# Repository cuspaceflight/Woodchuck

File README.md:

# Woodchuck
2015/2016 HAB project

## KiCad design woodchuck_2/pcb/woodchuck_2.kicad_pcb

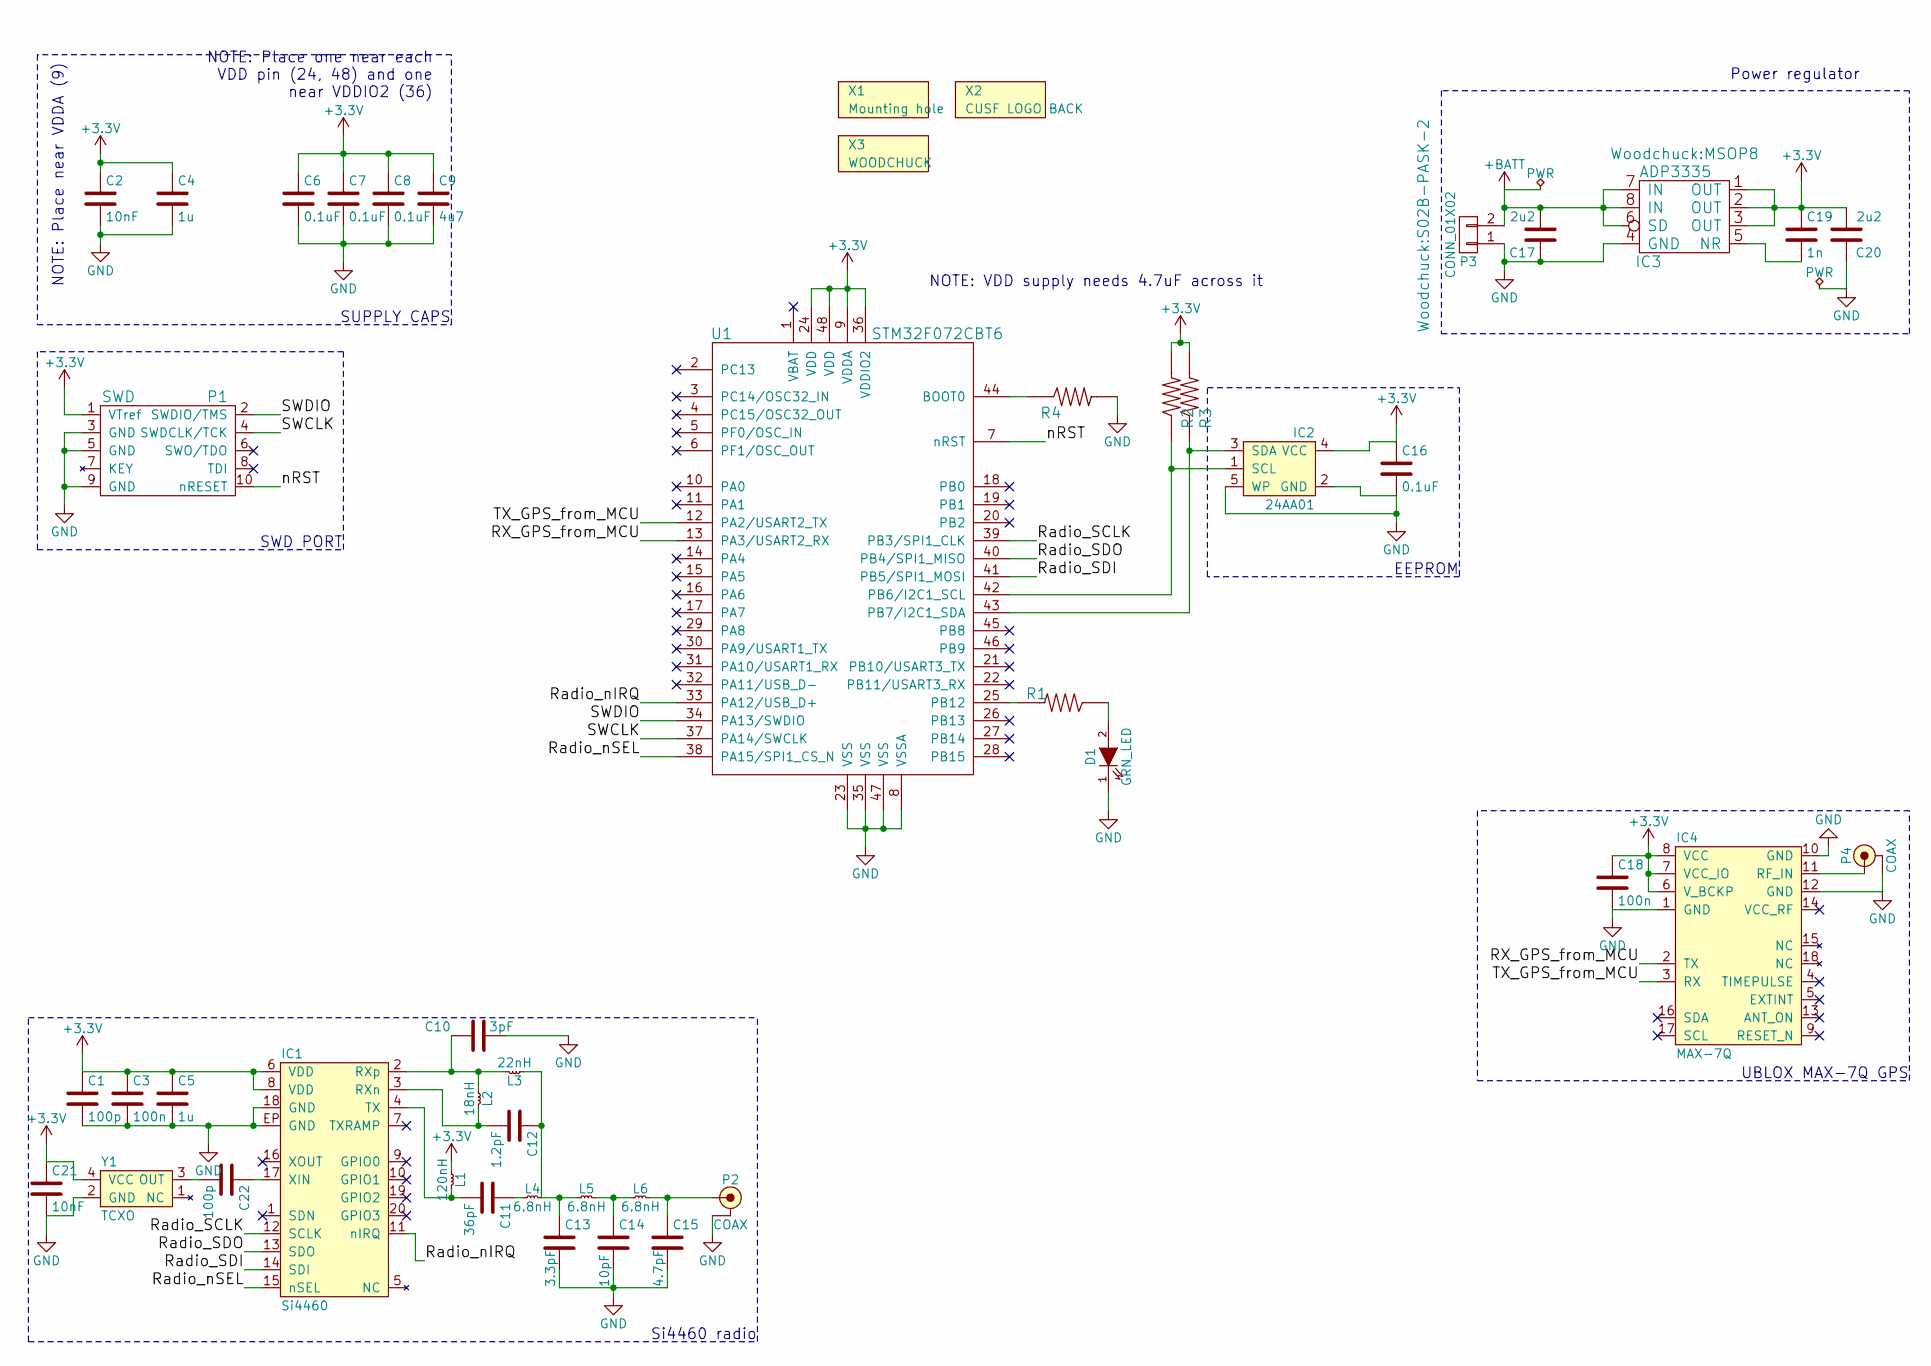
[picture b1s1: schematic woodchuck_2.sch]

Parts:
C1, C22: 100p; 0402; Digikey Value
C2, C21: 10nF; 0402; Digikey Value
C3, C18: 100n; 0402; Digikey Value
C4, C5: 1u; 0402; Digikey Value
C6, C7, C8, C16: 0.1uF; 0402; Digikey Value
C9: 4u7; 0402; Digikey Value
C10: 3pF; 0402; Digikey Value
C11: 36pF; 0402; Digikey Value
C12: 1.2pF; 0402; Digikey Value
C13: 3.3pF; 0402; Digikey Value
C14: 10pF; 0402; Digikey Value
C15: 4.7pF; 0402; Digikey Value
C17, C20: 2u2; 0603; Digikey Value
C19: 1n; 0402; Digikey Value
D1: GRN_LED; 0603-LED; Digikey Value
IC1: Si4460; QFN-20-EP-SI; Farnell 2462635
IC2: 24AA01; SOT-23-5; Farnell 1331269
IC3: ADP3335; MSOP8; Digikey Value
IC4: MAX-7Q; Digikey Value
L1: 120nH; 0603-L; Digikey Value
L2: 18nH; 0603-L; Digikey Value
L3: 22nH; 0603-L; Digikey Value
L4, L5, L6: 6.8nH; 0603-L; Digikey Value
P1: SWD; FTSH-105-01-F-D-K; Digikey Value
P2, P4: COAX; SMA-142-0701-801; Digikey Value
P3: CONN_01X02; S02B-PASK-2; Digikey Value
R1: 510; 0402; Digikey Value
R2, R3, R4: 10K; 0402; Digikey Value
U1: STM32F072CBT6; LQFP48; Digikey Value
X1: Mounting hole; M3_MOUNT
X2: CUSF LOGO BACK; cusf_logo_small; Digikey Value
X3: WOODCHUCK; Woodchuck_2; Digikey Value
Y1: TCXO; TG-5006CJ; Digikey Value

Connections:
+3V3: C1.1, C2.1, C3.1, C4.1, C5.1, C6.1, C7.1, C8.1, C9.1, C16.1, C18.1, C19.1, C20.2, C21.1, IC1.6 (VDD), IC1.8 (VDD), IC2.4 (VCC), IC3.1 (OUT), IC3.2 (OUT), IC3.3 (OUT), IC4.6 (V_BCKP), IC4.7 (VCC_IO), IC4.8 (VCC), L1.1, P1.1 (VTref), R2.1, R3.1, U1.9 (VDDA), U1.24 (VDD), U1.36 (VDDIO2), U1.48 (VDD), Y1.4 (VCC)
+BATT: C17.2, IC3.6 (SD), IC3.7 (IN), IC3.8 (IN), P3.2
/RX_GPS_from_MCU: IC4.2 (TX), U1.13 (PA3/USART2_RX)
/Radio_SCLK: IC1.12 (SCLK), U1.39 (PB3/SPI1_CLK)
/Radio_SDI: IC1.14 (SDI), U1.41 (PB5/SPI1_MOSI)
/Radio_SDO: IC1.13 (SDO), U1.40 (PB4/SPI1_MISO)
/Radio_nIRQ: IC1.11 (nIRQ), U1.33 (PA12/USB_D+)
/Radio_nSEL: IC1.15 (nSEL), U1.38 (PA15/SPI1_CS_N)
/SWCLK: P1.4 (SWDCLK/TCK), U1.37 (PA14/SWCLK)
/SWDIO: P1.2 (SWDIO/TMS), U1.34 (PA13/SWDIO)
/TX_GPS_from_MCU: IC4.3 (RX), U1.12 (PA2/USART2_TX)
/nRST: P1.10 (nRESET), U1.7 (nRST)
GND: C1.2, C2.2, C3.2, C4.2, C5.2, C6.2, C7.2, C8.2, C9.2, C10.2, C13.2, C14.2, C15.2, C16.2, C17.1, C18.2, C20.1, C21.2, D1.1 (K), IC1.18 (GND), IC1.EP (GND), IC2.2 (GND), IC2.5 (WP), IC3.4 (GND), IC4.1 (GND), IC4.10 (GND), IC4.12 (GND), P1.3 (GND), P1.5 (GND), P1.9 (GND), P2.2 (GND), P3.1, P4.2 (GND), R4.1, U1.8 (VSSA), U1.23 (VSS), U1.35 (VSS), U1.47 (VSS), Y1.2 (GND)
unnamed: C10.1, IC1.2 (RXp), L2.1, L3.2
unnamed: C11.1, L4.1
unnamed: C11.2, IC1.4 (TX), L1.2
unnamed: C12.1, C13.1, L3.1, L4.2, L5.1
unnamed: C12.2, IC1.3 (RXn), L2.2
unnamed: C14.1, L5.2, L6.1
unnamed: C15.1, L6.2, P2.1 (RF)
unnamed: C19.2, IC3.5 (NR)
unnamed: C22.1, IC1.17 (XIN)
unnamed: C22.2, Y1.3 (OUT)
unnamed: D1.2 (A), R1.2
unnamed: IC2.1 (SCL), R2.2, U1.42 (PB6/I2C1_SCL)
unnamed: IC2.3 (SDA), R3.2, U1.43 (PB7/I2C1_SDA)
unnamed: IC4.11 (RF_IN), P4.1 (RF)
unnamed: R1.1, U1.25 (PB12)
unnamed: R4.2, U1.44 (BOOT0)

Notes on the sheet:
Power regulator
NOTE: Place one near each VDD pin (24, 48) and one near VDDIO2 (36)
NOTE: Place near VDDA (9)
NOTE: VDD supply needs 4.7uF across it
SWD PORT
SUPPLY CAPS
EEPROM
UBLOX MAX-7Q GPS
Si4460 radio

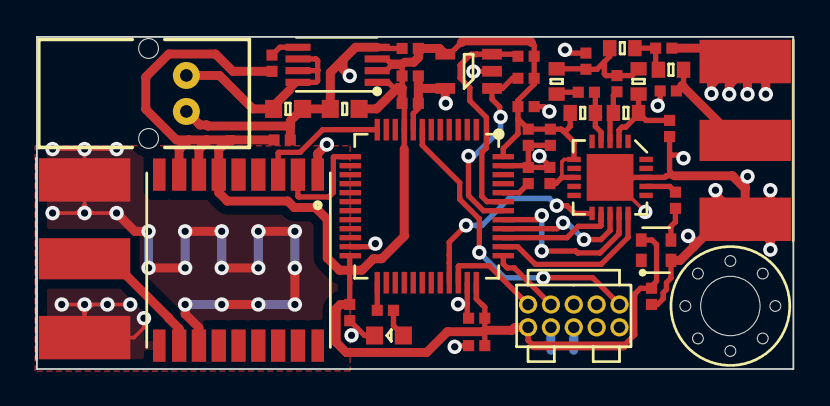
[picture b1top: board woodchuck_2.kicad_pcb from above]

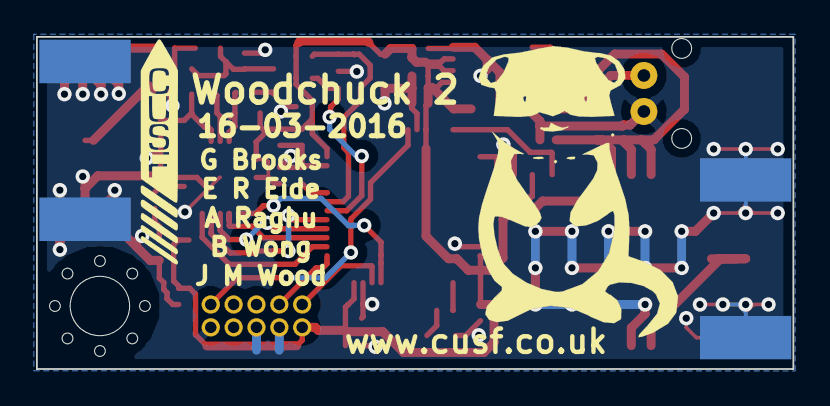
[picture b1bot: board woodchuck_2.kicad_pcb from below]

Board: 2 copper layers, 42.0 x 18.5 mm, 46 parts (2 on the bottom side), 29 nets.

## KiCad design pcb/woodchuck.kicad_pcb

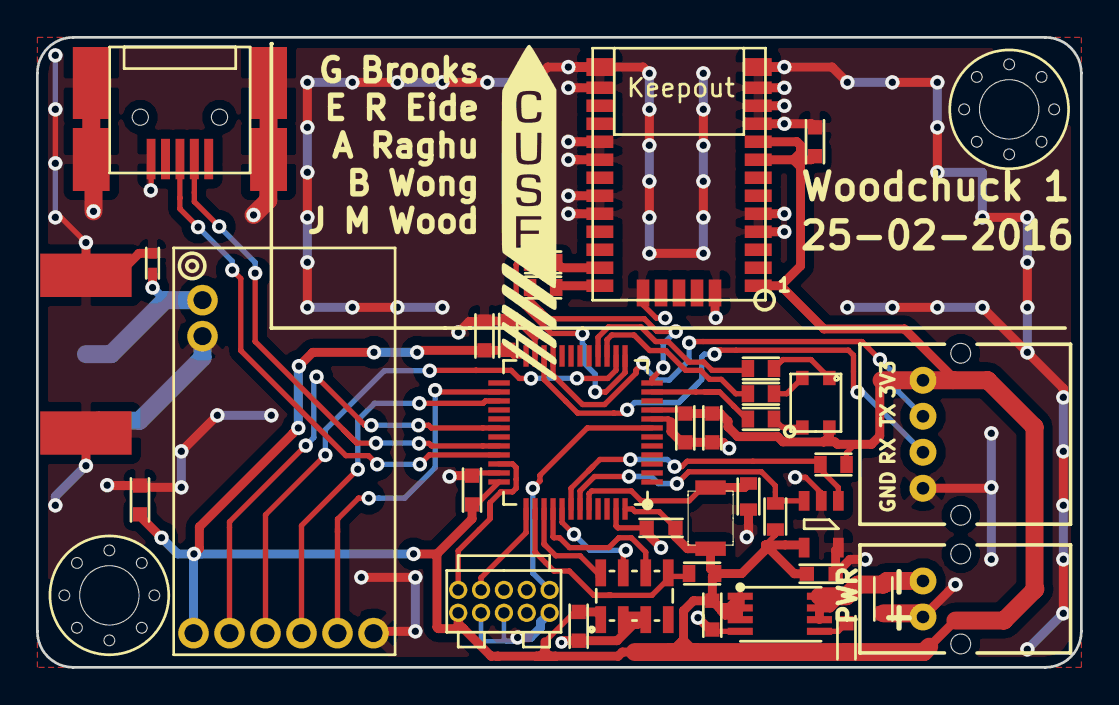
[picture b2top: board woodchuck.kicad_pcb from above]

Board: 2 copper layers, 58.0 x 35.0 mm, 40 parts (1 on the bottom side), 34 nets.

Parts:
A301: SMA; SMA-142-0701-801
C1, C402, C403, C404: 0.1uF; C0603
C101, C103: 2u2; C0603
C102: 1n; C0603
C201, C301, C601: 100n; C0603
C401: 10nF; C0603
C405: 1u; C0603
C406: 4u7; C0603
D301: CGA0402MLC-12G; R0402
D401: LED_RABG; CREE_RGB_LED
IC1: 24AA01; SOT-23-5
IC101: ADP3335; MSOP8
IC201: u-blox_CAM-M8Q; UBLOX_CAM_M8Q
IC601: MS5611-01BA03; MS5611-01BA
J401: JSTA-4; S04B-PASK-2
P101: CONN_01X02; S02B-PASK-2
P401: SWD; FTSH-105-01-F-D-K
P402: USB_OTG; MOLEX_67503_1020_MINI_USB
R1, R2, R404: 10K; 0603
R201, R202: 220; 0603
R401, R402, R403: 510; 0603
R601: 10k; 0603
SW401: SPST; B3U-1000P_switch
U301: Radiometrix_MTX2; MTX2
U401: STM32F072CBT6; LQFP48
X401, X402: Mounting hole; M3_MOUNT
X403: CUSF LOGO; cusf_logo
X404: CUSF LOGO BACK; cusf_logo_full

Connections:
+3V3: C1.1, C102.1, C103.1, C201.2, C301.1, C401.1, C402.1, C403.1, C404.1, C405.1, C406.1, C601.1, D401.2, IC1.4, IC101.1, IC101.2, IC101.3, IC201.1, IC201.8, IC201.9, IC601.1, J401.1, P401.1, R1.1, R2.1, R601.1, SW401.2, U301.3, U401.9, U401.24, U401.36, U401.48
+BATT: C101.2, IC101.6, IC101.7, IC101.8, P101.1
/GPS/GPS_FROM_MCU: R202.1, U401.12
/GPS/GPS_TO_MCU: R201.1, U401.13
/Radio/MTX2_EN/PGM: U301.4, U401.30
/Radio/MTX2_P0: U301.7, U401.26
/Radio/MTX2_P1: U301.6, U401.27
/Radio/MTX2_TXD: U301.5, U401.14
/barometer/BARO_CS: IC601.5, R601.2, U401.38
/barometer/BARO_MISO: IC601.6, U401.40
/barometer/BARO_MOSI: IC601.7, U401.41
/microcontroller/BARO_CLK: IC601.8, U401.39
/microcontroller/BOOT0: R404.1, SW401.1, U401.44
/microcontroller/EXT_RX: J401.3, U401.22
/microcontroller/EXT_TX: J401.2, U401.21
/microcontroller/SWCLK: P401.4, U401.37
/microcontroller/SWDIO: P401.2, U401.34
/microcontroller/USB_D+: P402.3, U401.33
/microcontroller/USB_D-: P402.2, U401.32
/microcontroller/nRST: P401.10, U401.7
GND: A301.2, A301.3, A301.4, A301.5, C1.2, C101.1, C103.2, C201.1, C301.2, C401.2, C402.2, C403.2, C404.2, C405.2, C406.2, C601.2, D301.2, IC1.2, IC1.5, IC101.4, IC201.4, IC201.5, IC201.10, IC201.11, IC201.12, IC201.13, IC201.14, IC201.15, IC201.18, IC201.19, IC201.21, IC201.22, IC201.27, IC201.31, IC601.2, IC601.3, J401.4, P101.2, P401.3, P401.5, P401.9, P402.5, P402.6, R404.2, U301.2, U301.8, U401.8, U401.23, U401.35, U401.47
unnamed: A301.1, D301.1, U301.1
unnamed: C102.2, IC101.5
unnamed: D401.1, R401.1
unnamed: D401.3, R403.1
unnamed: D401.4, R402.1
unnamed: IC1.1, R1.2, U401.42
unnamed: IC1.3, R2.2, U401.43
unnamed: IC201.16, IC201.17
unnamed: IC201.25, R201.2
unnamed: IC201.26, R202.2
unnamed: R401.2, U401.11
unnamed: R402.2, U401.15
unnamed: R403.2, U401.16

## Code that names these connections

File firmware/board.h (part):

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 *
 * PA0  - PIN0                         (unused).
 * PA1  - LED_RED                      (output, opendrain).
 * PA2  - GPS_TX                       (af1).
 * PA3  - GPS_RX                       (af1).
 * PA4  - RADIO_TX_DATA                (analog).
 * PA5  - LED_GREEN                    (output, opendrain).
 * PA6  - LED_BLUE                     (output, opendrain).
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 * PA9  - RADIO_EN_PIN                 (af1).
 * PA10 - USART_1_RX                   (af1).
 * PA11 - PIN11                        (unused).
 * PA12 - PIN12                        (unused).
 * PA13 - SWDIO                        (af0).
 * PA14 - SWCLK                        (af0).
 * PA15 - BARO_NCS                     (af0).
*/
#define VAL_GPIOA_MODER                (PIN_MODE_INPUT(GPIOA_PIN0) | \
                                        PIN_MODE_OUTPUT(GPIOA_LED_RED) | \
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 * PB0  - PIN0                         (unused).
 * PB1  - PIN1                         (unused).
 * PB2  - PIN2                         (unused).
 * PB3  - BARO_CLK                     (af0).
 * PB4  - BARO_MISO                    (af0).
 * PB5  - BARO_MOSI                    (af0).
 * PB6  - PIN6                         (unused).
 * PB7  - PIN7                         (unused).
 * PB8  - PIN8                         (unused).
 * PB9  - PIN9                         (unused).
 * PB10 - PIN10                        (unused).
 * PB11 - PIN11                        (unused).
 * PB12 - PIN12                        (unused).
 * PB13 - RADIO_CHANNEL_LSB            (output).
 * PB14 - RADIO_CHANNEL_MSB            (output).
 * PB15 - PIN15                        (unused).
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
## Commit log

2015-11-05 Added folders for PCB design and Firmware
2015-11-05 Added a KiCAD project
2015-11-05 Updated the info for the PCB
2015-11-05 Update pcbinfo.txt
    Added GPS info
2015-11-20 Create u-blox CAM-M8Q component and add avionics14 libraries to pcb folder
2015-11-26 Ani- Added supersheetsgit status
2015-11-27 Add radiometrix mtx2 schematic component
2015-11-29 Add STM32F072CBT6 library and microcontroller sheet
2015-11-29 Add SWD port to microcontroller sheet
2015-11-29 Add JSTA-4 connector
2015-11-29 Add USB connector to microcontroller sheet
2015-11-29 Add bootloader select switch to microcontroller sheet
2015-12-01 Add MTX2 circuit and add a sheet for power supply/regulation
2015-12-01 Added power regulation. Using component ADP3335 as used in Avionics14.
2015-12-02 Add MTX2 footprint library from m2r
2015-12-02 Fix missing microcontroller.sch
2015-12-02 Added changes to barometer
2015-12-02 Add GPS footprint
2015-12-02 Added psu to gps
2015-12-02 Modify pin assignments of MCU
2015-12-04 Add LQFP48 footprint for microcontroller
2015-12-04 Add silk screen to LQFP48 footprint
2015-12-05 Assigned a few footprints. Still need to find out if it is possible to hide all footprint names from the schematics.
2016-01-18 Add some footprints
2016-01-18 Fix swapped EN / TX pins on radio
2016-01-19 Add GPS driver for uBlox M8Q
2016-01-19 Add mini USB footprint
2016-01-28 Change some heirarchical pin directions
2016-01-28 Update heirarchical pin directions
2016-01-28 Begin routing GPS
2016-01-30 Finished schematics for GPS. TODO: check DSEL, and that RX TX are connected correctly. Make sure capacitor and resistor values are ok.
2016-01-30 Change decoupling cap to 100nF (like other projects) and connect V_BCKP to VCC
2016-01-30 Generated net list (only two footprints remaining), added a few footprints, started rough estimate of PCB size
2016-02-01 Added a main.c file to the folder with the code for Joey, no other changes.
2016-02-01 Removed antenna for GPS module, connected ANT to RF-IN
2016-02-01 footprint for switch
2016-02-01 Generated a new netlist
2016-02-01 Added a footprint and changed footprints for resistors to the 0603 SMD footprint.
2016-02-01 Begin placing PCB components
2016-02-01 added footprint to bootloader select
2016-02-01 Connect hierarchical pins
2016-02-01 Fix watchdog timer, interrupts enable. Add interrupts header
2016-02-01 Started Baro driver firmware
2016-02-01 Added libopencm3 as submodule to Woodchuck
2016-02-02 Fix indent in gps.c
2016-02-04 Added gitignore
2016-02-04 Fix LED circuit and radio tx/rx labels, start LED driver code
2016-02-04 Fix barometer hierarchical pins and add Farnell numbers to components
2016-02-05 Connect MTX2 parallel channel select pins to the MCU
2016-02-06 Added a half finished baro driver
2016-02-07 Added radio driver
2016-02-07 Fixed some syntactic errors
2016-02-07 Fixed a couple more syntactic errors
2016-02-07 Add eeprom driver (untested)
2016-02-08 Fix eeprom include
2016-02-08 Add dword read/write to eeprom driver
2016-02-08 Add new eeprom driver calls to main.c
2016-02-08 Continued working on the baro driver
2016-02-08 Should be ready to do core functionality. Still a few TODOs
2016-02-08 Fixed a few bugs
2016-02-08 It compilesgit status
2016-02-08 Imported a clock functionality from OKGO2
2016-02-08 Adapted code for Woodchuck
2016-02-08 included timer in baro file
2016-02-08 TODO: clock doesn't compile due to CM_ATOMIC_BLOCK macro does not expand correctly in this version of C
2016-02-09 Add to LED driver
2016-02-09 Tidy up led number to pin number conversion, use enum for led number argument in led_set function
2016-02-09 Let systick handle timer interrupts
2016-02-11 Add agg-kicad submodule
2016-02-11 Added a missing footprint.
2016-02-11 Fixed the planes
2016-02-11 Added Makefile and fixed radio bugs- now compiles
2016-02-12 Fix eeprom.c/.h typos and missing #defines
2016-02-13 Update agg-kicad to latest version
2016-02-13 Update STM32F0702CBT6 library
2016-02-13 Add 24AA01 EEPROM and add agg-kicad library
2016-02-13 Add I2C pull-up resistors
2016-02-13 Ran ERC and regenerated netlist
2016-02-13 Fixed some errors in the schematics
2016-02-14 Bug fixes in radio driver
2016-02-15 Worked on PCB layout
2016-02-16 Continued routing PCB
2016-02-16 Continued routing PCB, changed order of LEDs
2016-02-16 All components on board, check Radio to MCU connection before proceeding
2016-02-17 Added a few capacitors, moved radio_tx tO DAC out
2016-02-17 regenerated and imported netlist
2016-02-17 Included the changes in the schematics
2016-02-17 PCB layout almost done. Add silkscreen and look over.
2016-02-17 Added logo and names to silk screen.
2016-02-17 Fixed edge cuts
2016-02-25 Finished layout with silkscreen
2016-02-29 Added a few missing datasheets and Farnell codes. Still missing GPS and MTX Farnell entry
2016-03-01 Hide footprints on schematic, fix overlaps
2016-03-01 Fix some layout issues
2016-03-01 Reorganise files in Woodchuck-2 branch
2016-03-02 Tidy up files in branch, add radio and GPS to schematic, remove barometer, USART, USB
2016-03-10 Update master
2016-03-10 libopencm3 now builds! Added Makefile to directory
2016-03-10 Fixed vias to correct sizes, moved some components further apart from each other
2016-03-10 Fixed issue with linker script naming
2016-03-10 last commit before reloading net list
2016-03-10 Fixed all DRC errors
2016-03-10 Generated gerbers, DONE!
2016-03-13 Tidy up folders
2016-03-13 Use KIPRJMOD in footprint library paths
2016-03-13 Actually delete duplicates this time
2016-03-15 Change components to 0402, add farnell numbers and use different TCXO
2016-03-16 Place components on board
2016-03-16 Route Woodchuck 2
2016-05-08 Added Farnell codes for capacitors
2016-05-08 Added BOM
2016-10-23 Manually bodge the BOM with smaller resistors for the RGB led
2016-10-23 Forgot to change R402, R403 values in BOM
2016-10-31 Tidy up fields to fix bom errors
2016-11-05 First makefile attempt
2016-11-05 Work on makefile
2016-11-05 Rename BINARY in Makefile, update rules.mk
2016-11-12 Begin fixing (many) bugs
2016-11-19 Cleanup compiled files
2016-11-19 Add Chibios, remove libopencm3
2016-11-19 Setup ChibiOS
2016-11-19 Start conversion of LED driver to ChibiOS.
2016-11-28 Port EEPROM driver to ChibiOS
2016-12-09 Convert gps driver to chibios
2016-12-11 Correct typo
2016-12-11 Port barometer driver back to chibios
2017-02-03 Remove interrupts.h stuff from main.c
2017-02-07 Update main.c, use i2cv2 driver for eeprom, fix some compiler errors
2017-02-12 Port LED driver to ChibiOS, make it build with some warnings
2017-03-16 Add dfu to makefile
2017-03-20 Add Black Magic commands to makefile
    Nicked from m3dl extpressure
2017-05-14 Bug fixes and begin porting/finishing mtx2 driver
2017-05-14 Fix some errors with chibios setup
2017-05-14 Futher progress with radio driver
2017-05-14 Update makefile
2017-05-14 Complete first radio driver attempt
2017-10-29 Update LED driver to use its own thread and fix gps serial config
2017-10-29 Minor changes to LED driver
2017-10-29 More LED driver tidying
2017-10-29 More LED bug fixes
2017-11-09 More LED bugfixes
2017-11-19 Final commit before using TOAD's gps driver
2017-11-19 Begin stripping down TOAD gps driver for HAB use
2017-11-19 Modify TOAD gps driver for woodchuck
2017-11-19 Tidy up old code

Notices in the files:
firmware/board.h:
ChibiOS - Copyright (C) 2006..2016 Giovanni Di Sirio
Licensed under the Apache License, Version 2.0 (the "License");
